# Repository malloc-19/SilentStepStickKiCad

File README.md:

# SilentStepStickKiCad
SilentStepStick TMC2209 imported to KiCad

Imported https://github.com/watterott/SilentStepStick into KiCad.
Added 3D Models from KiCads Library.

Attribution goes to https://github.com/watterott.

Open-Source and released under the Creative Commons Attribution Share-Alike License.
https://creativecommons.org/licenses/by-sa/4.0/

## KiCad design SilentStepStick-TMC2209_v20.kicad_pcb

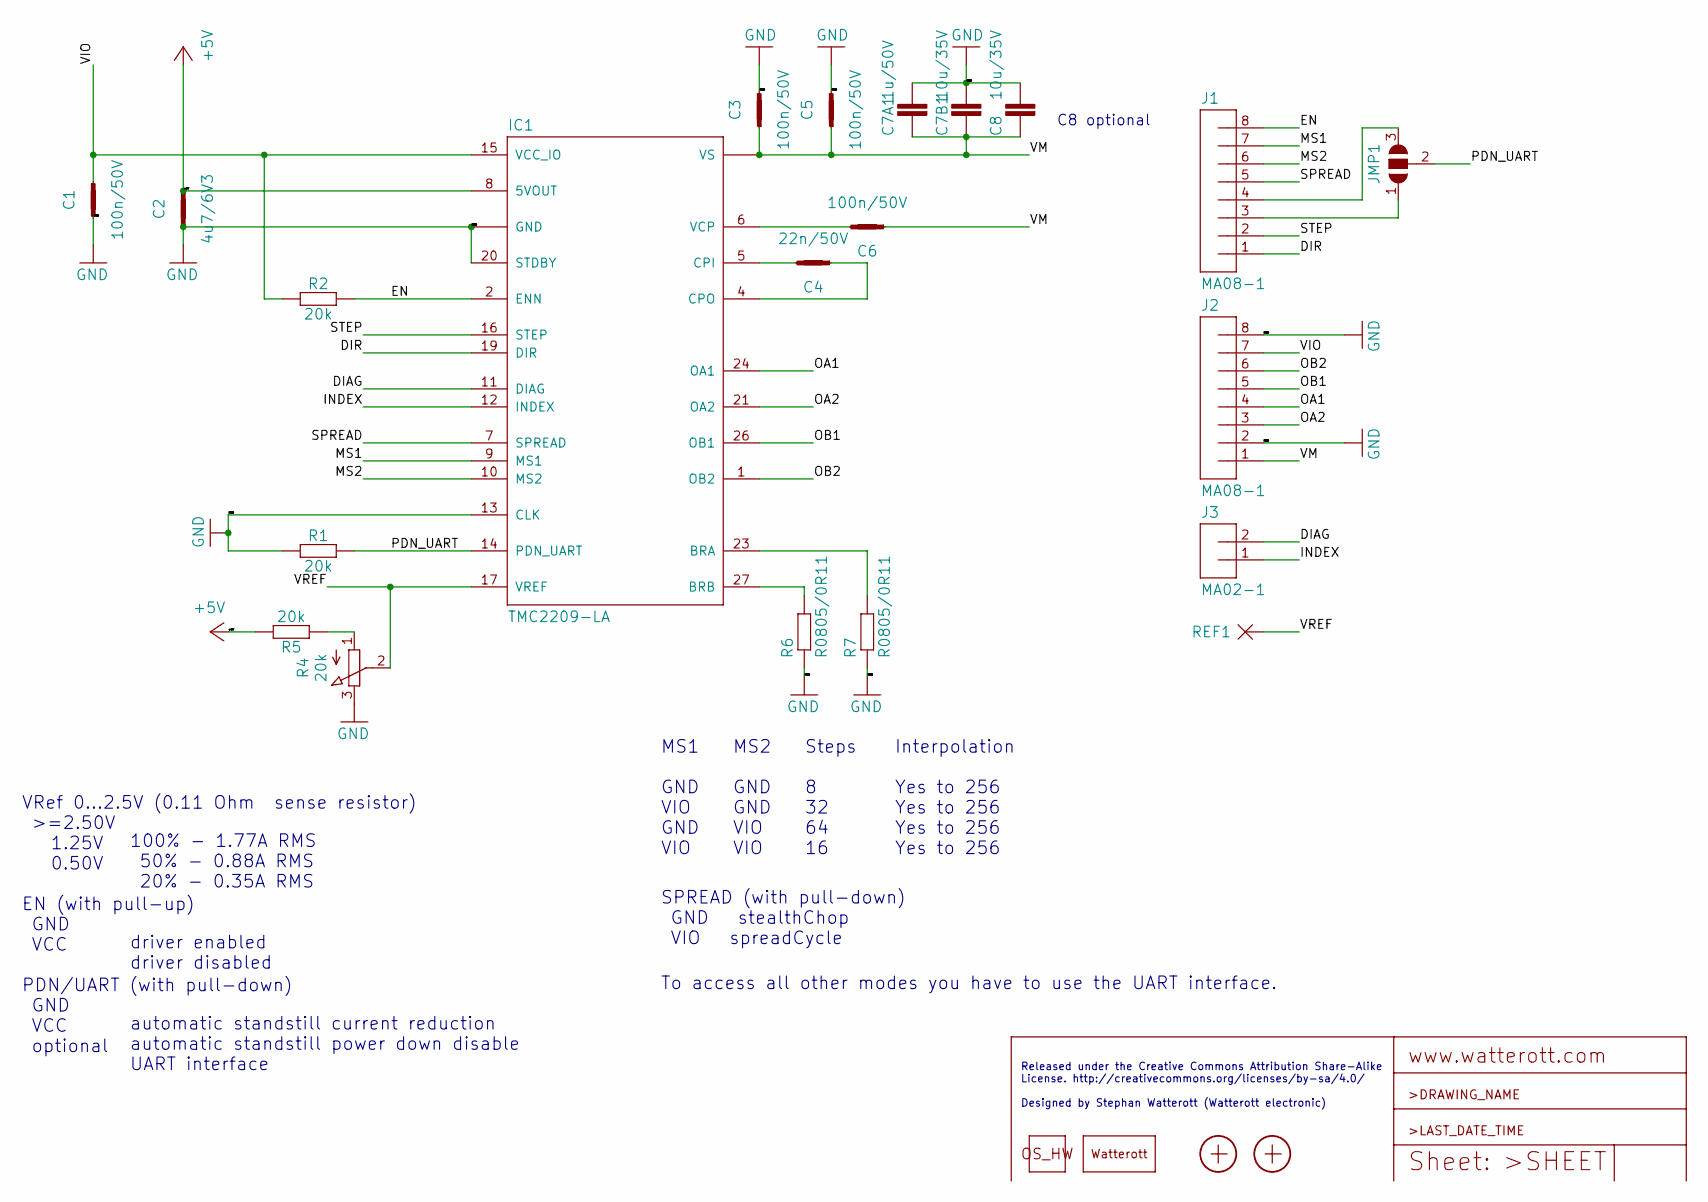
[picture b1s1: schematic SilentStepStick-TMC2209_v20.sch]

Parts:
C1, C3, C5, C6: 100n/50V; C0402
C2: 4u7/6V3; C0402
C4: 22n/50V; C0402
C7A1: 1u/50V; C0805
C7B1, C8: 10u/35V; C1206
IC1: TMC2209-LA; QFN28-PAD3.7
J1, J2: MA08-1
J3: MA02-1
JMP1: JUMPER3-0402-NC; JUMPER3-0402_NC
LOGO3: LOGO_SPARK-2; SPARK_2MM
LOGO4: LOGO_OSHW-2; OSHW_2MM
R1, R2, R5: 20k; C0402
R4: 20k; POT_EVM3R
R6, R7: R0805/0R11; M0805
REF1: PAD-0.6-1.1
X1, X2: PASSER-04; PASSER_04MM

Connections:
+5V: C2.2, IC1.8 (5VOUT), R5.2
/DIAG: IC1.11 (DIAG), J3.2
/DIR: IC1.19 (DIR), J1.1
/EN: IC1.2 (ENN), J1.8, R2.2
/INDEX: IC1.12 (INDEX), J3.1
/MS1: IC1.9 (MS1), J1.7
/MS2: IC1.10 (MS2), J1.6
/OA1: IC1.24 (OA1), J2.4
/OA2: IC1.21 (OA2), J2.3
/OB1: IC1.26 (OB1), J2.5
/OB2: IC1.1 (OB2), J2.6
/PDN_UART: IC1.14 (PDN_UART), JMP1.2, R1.2
/SPREAD: IC1.7 (SPREAD), J1.5
/STEP: IC1.16 (STEP), J1.2
/VIO: C1.2, IC1.15 (VCC_IO), J2.7, R2.1
/VM: C3.1, C5.1, C6.1, C7A1.1, C7B1.1, C8.1, IC1.22 (VS), IC1.28 (VS), J2.1
/VREF: IC1.17 (VREF), R4.2 (S), REF1.1
GND: C1.1, C2.1, C3.2, C5.2, C7A1.2, C7B1.2, C8.2, IC1.3 (GND), IC1.13 (CLK), IC1.18 (GND), IC1.20 (STDBY), IC1.TP (GND), J2.2, J2.8, R1.1, R4.3 (E), R6.1, R7.1
unnamed: C4.1, IC1.4 (CPO)
unnamed: C4.2, IC1.5 (CPI)
unnamed: C6.2, IC1.6 (VCP)
unnamed: IC1.23 (BRA), R7.2
unnamed: IC1.27 (BRB), R6.2
unnamed: J1.3, JMP1.1
unnamed: J1.4, JMP1.3
unnamed: R4.1 (A), R5.1

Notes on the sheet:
Released under the Creative Commons Attribution Share-Alike License. http://creativecommons.org/licenses/by-sa/4.0/ Designed by Stephan Watterott (Watterott electronic)
VRef 0...2.5V (0.11 Ohm sense resistor) >=2.50V 1.25V 0.50V EN (with pull-up) GND VCC PDN/UART (with pull-down) GND VCC optional
100% - 1.77A RMS 50% - 0.88A RMS 20% - 0.35A RMS driver enabled driver disabled automatic standstill current reduction automatic standstill power down disable UART interface
MS1 GND VIO GND VIO
MS2 GND GND VIO VIO
Steps 8 32 64 16
Interpolation Yes to 256 Yes to 256 Yes to 256 Yes to 256
SPREAD (with pull-down) GND stealthChop VIO spreadCycle
To access all other modes you have to use the UART interface.
C8 optional

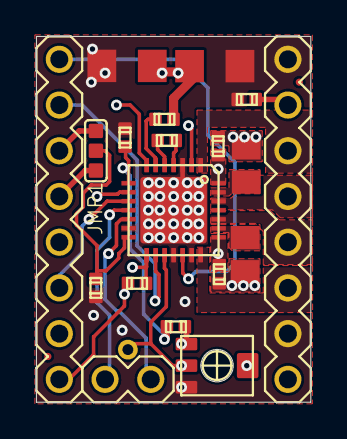
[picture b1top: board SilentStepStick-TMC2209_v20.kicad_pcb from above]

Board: 4 copper layers, 15.2 x 20.3 mm, 24 parts (0 on the bottom side), 26 nets.

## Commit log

2020-05-31 Added .gitignore
2020-05-31 Initial Upload
2020-05-31 Updated readme with License
